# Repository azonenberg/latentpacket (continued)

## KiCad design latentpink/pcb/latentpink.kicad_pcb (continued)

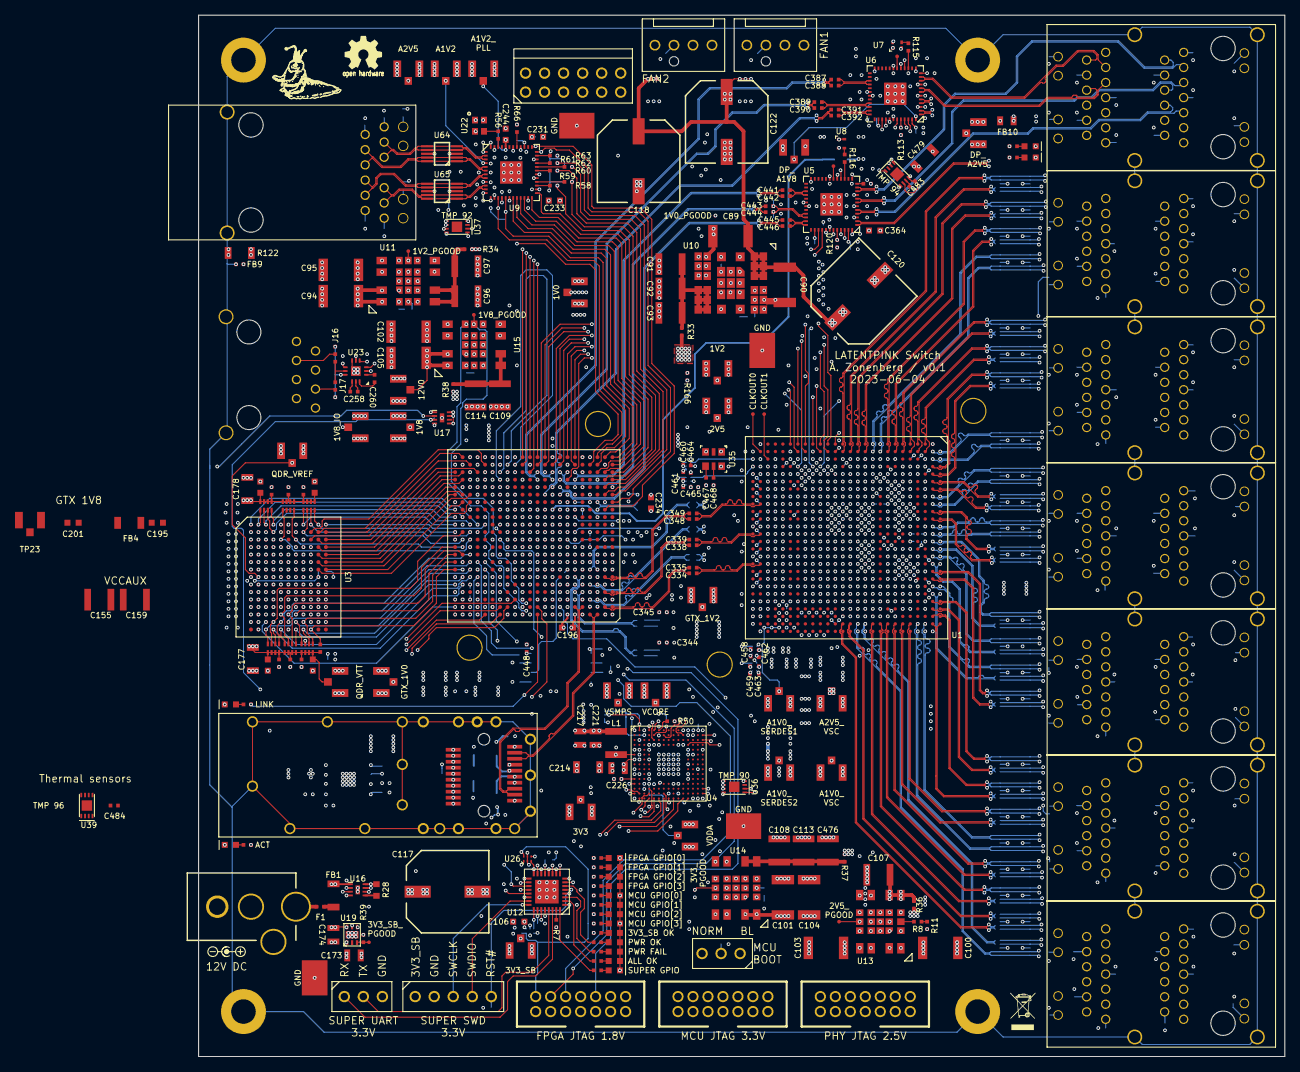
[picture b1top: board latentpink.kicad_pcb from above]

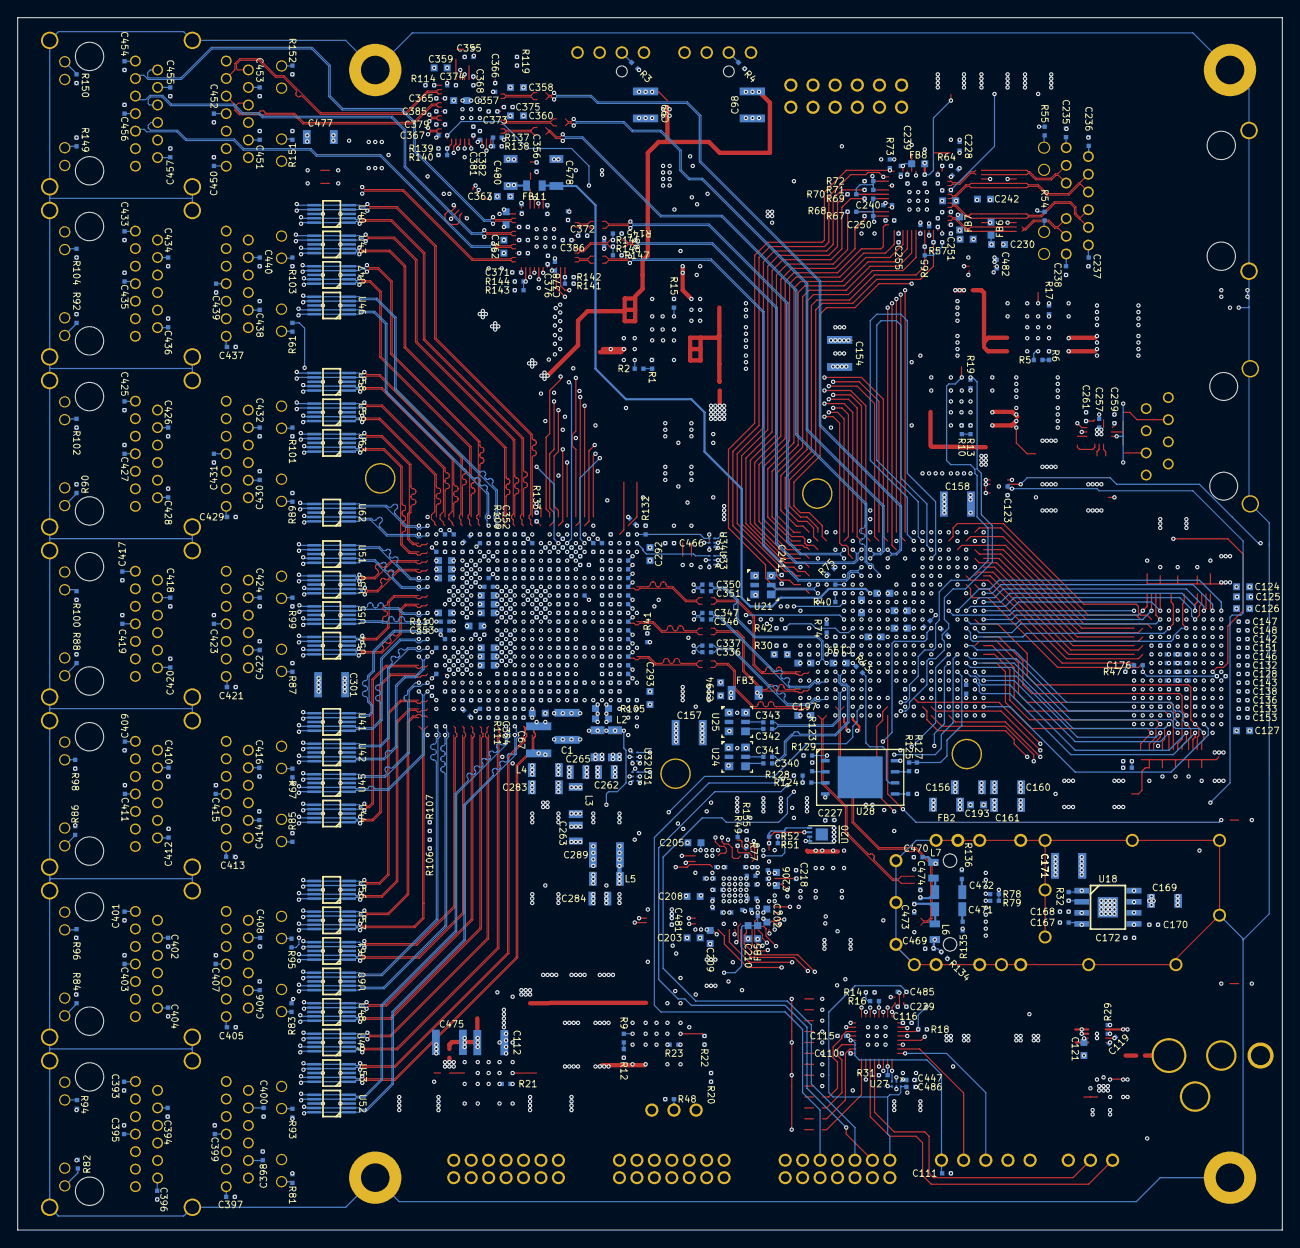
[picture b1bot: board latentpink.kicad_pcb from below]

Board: 8 copper layers, 145.0 x 139.0 mm, 827 parts (563 on the bottom side), 686 nets.

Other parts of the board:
C171#2: 220 uF; EIA_1210_CAP_NOSILK

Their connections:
/GND: C171#2.2; also elsewhere on the board
/QDR_VTT: C171#2.1; also elsewhere on the board

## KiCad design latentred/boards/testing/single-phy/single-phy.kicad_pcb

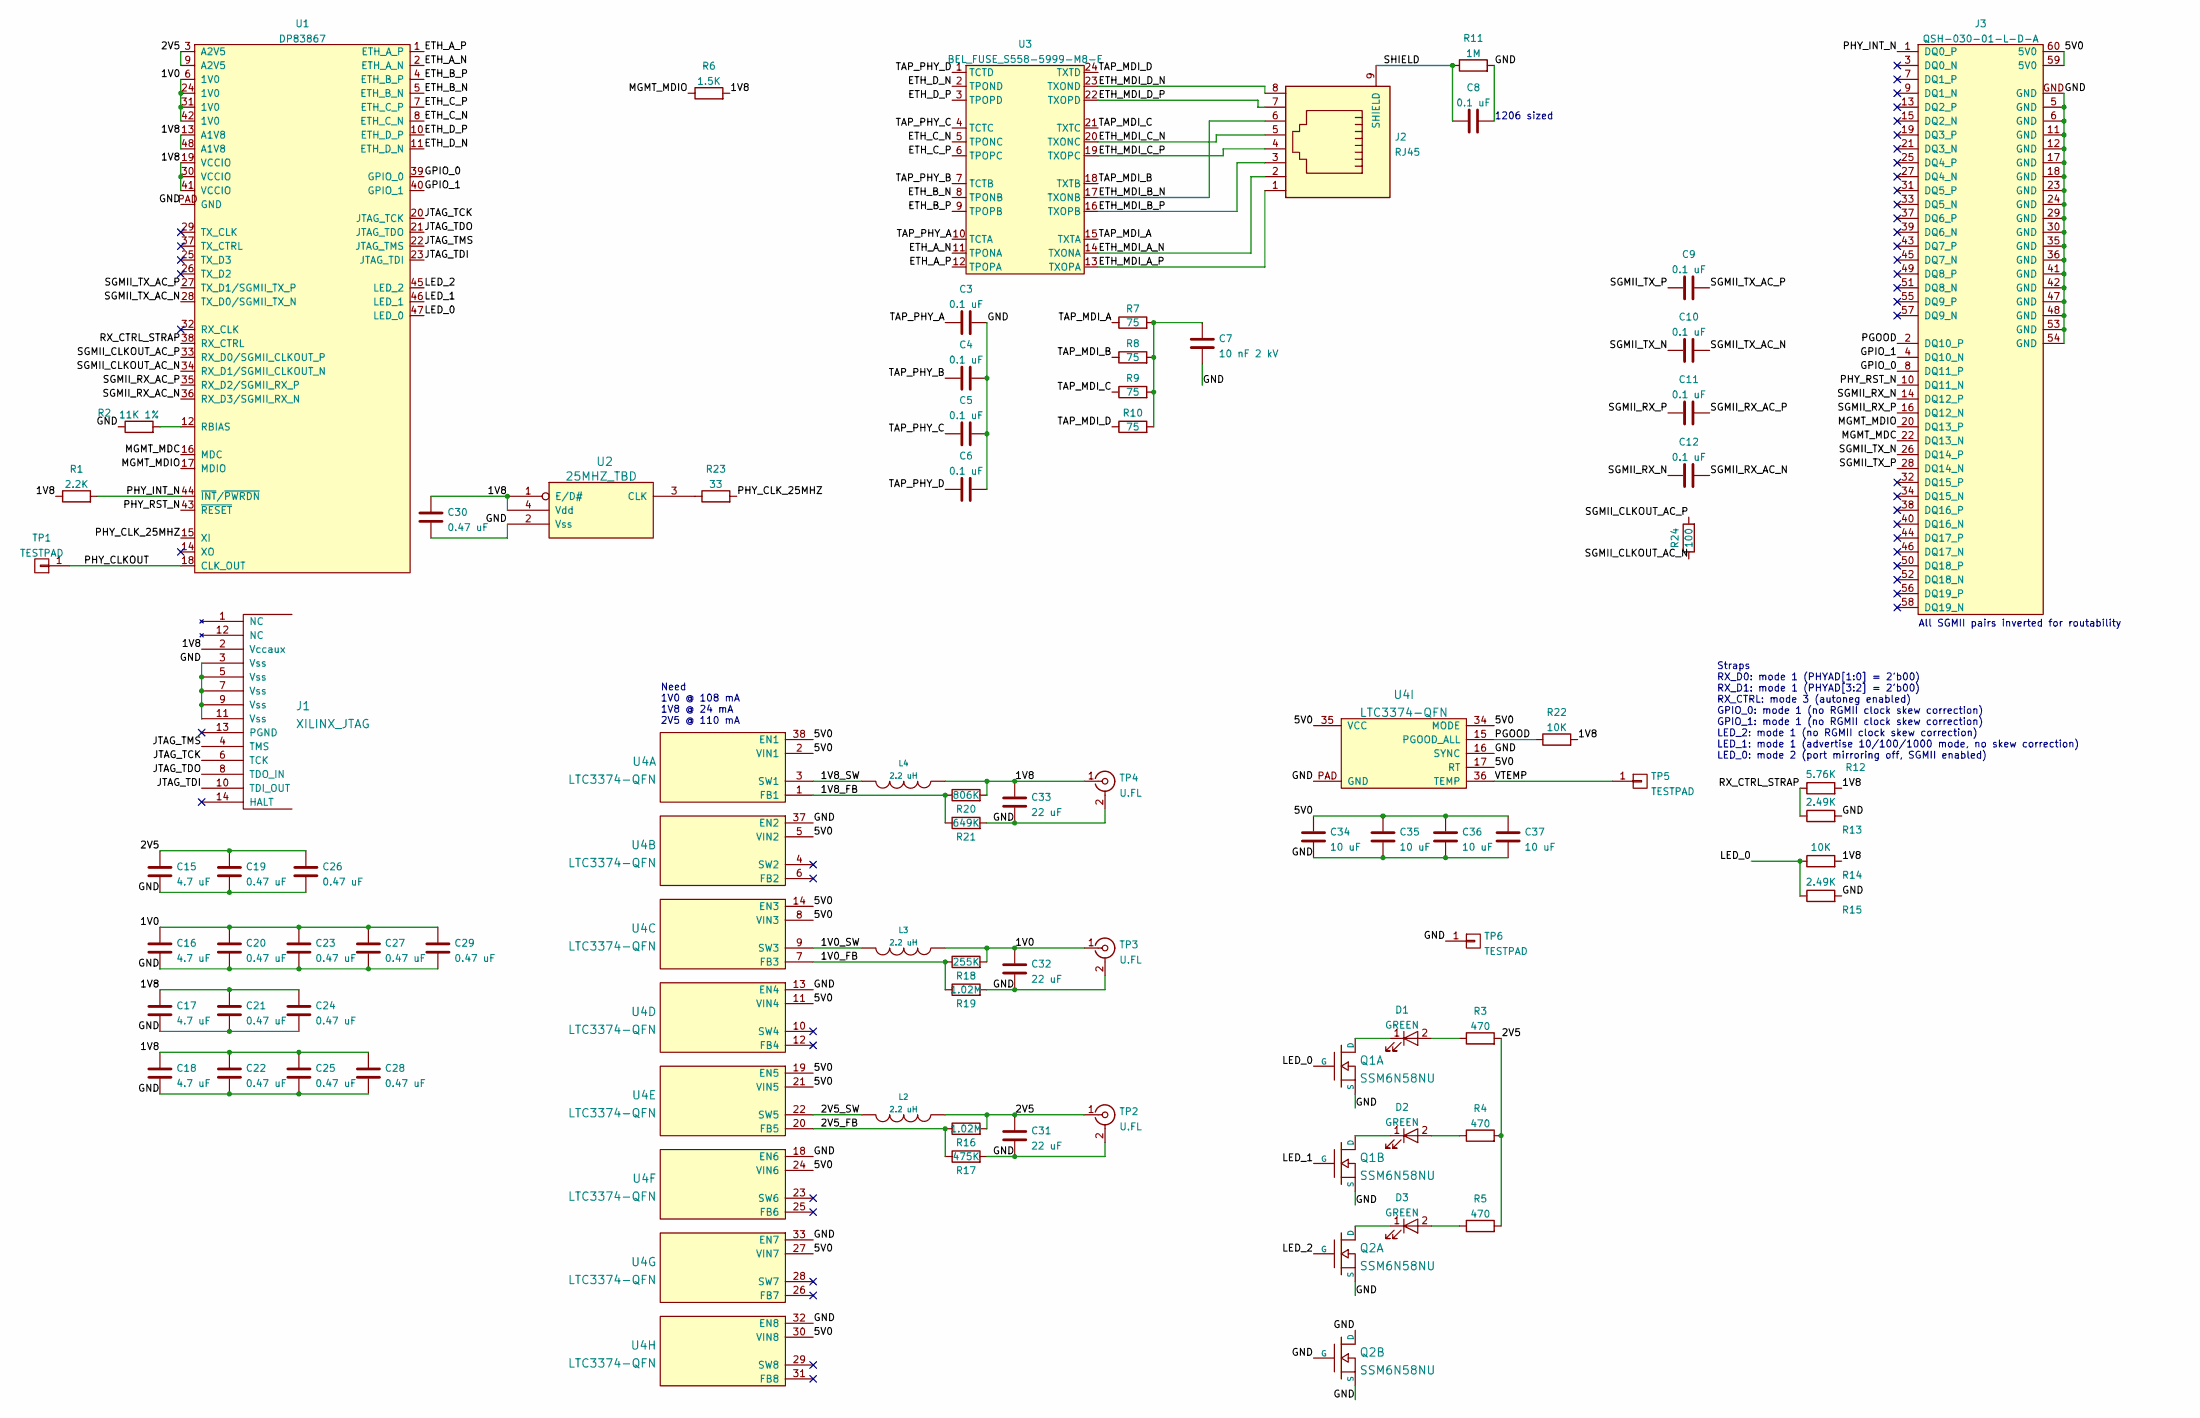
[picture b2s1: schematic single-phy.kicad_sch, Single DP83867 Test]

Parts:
C3, C4, C5, C6, C9, C10, C11, C12: 0.1 uF; EIA_0402_CAP_NOSILK
C7: 10 nF 2 kV; EIA_1812_CAP_NOSILK
C8: 0.1 uF; EIA_1206_CAP_NOSILK
C15, C16, C17, C18: 4.7 uF; EIA_0603_CAP_NOSILK
C19, C20, C21, C22, C23, C24, C25, C26, C27, C28, C29, C30: 0.47 uF; EIA_0402_CAP_NOSILK
C31, C32, C33: 22 uF; EIA_1206_CAP_NOSILK
C34, C35, C36, C37: 10 uF; EIA_0805_CAP_NOSILK
D1, D2, D3: GREEN; EIA_0603_LED
J1: XILINX_JTAG; XILINX_JTAG_PTH_MOLEX_0878311420
J2: RJ45; CONN_RJ45_BELSTEWART_SS-7188S-A-PG4-1-BA-xx
J3: QSH-030-01-L-D-A; CONN_SAMTEC_QSH-030-01-L-D-A
L2, L3, L4: 2.2 uH; EIA_1210_CAP_NOSILK
Q1, Q2: SSM6N58NU; DFN_6_0.65MM_2x2MM_GDS
R1: 2.2K; EIA_0402_RES_NOSILK
R2: 11K 1%; EIA_0402_RES_NOSILK
R3, R4, R5: 470; EIA_0402_RES_NOSILK
R6: 1.5K; EIA_0402_RES_NOSILK
R7, R8, R9, R10: 75; EIA_0402_RES_NOSILK
R11: 1M; EIA_1206_CAP_NOSILK
R12: 5.76K; EIA_0402_RES_NOSILK
R13, R15: 2.49K; EIA_0402_RES_NOSILK
R14, R22: 10K; EIA_0402_RES_NOSILK
R16, R19: 1.02M; EIA_0402_RES_NOSILK
R17: 475K; EIA_0402_RES_NOSILK
R18: 255K; EIA_0402_RES_NOSILK
R20: 806K; EIA_0402_RES_NOSILK
R21: 649K; EIA_0402_RES_NOSILK
R23: 33; EIA_0402_RES_NOSILK
R24: 100; EIA_0402_RES_NOSILK
TP1, TP5: TESTPAD; TESTPOINT_SMT_0.5MM
TP2, TP3, TP4: U.FL; CONN_U.FL_TE_1909763-1
TP6: TESTPAD; TESTPOINT_SMT_KEYSTONE_5016
U1: DP83867; QFN_48_0.5MM_7x7MM
U2: 25MHZ_TBD; OSCILLATOR_2.0x1.6
U3: BEL_FUSE_S558-5999-M8-F; BELFUSE_S558-5999-M8-F
U4: LTC3374-QFN; QFN_38_0.5MM_5x7MM

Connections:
/1V0: C16.1, C20.1, C23.1, C27.1, C29.1, C32.1, L3.1, R18.2, TP3.1 (In), U1.6 (1V0), U1.24 (1V0), U1.31 (1V0), U1.42 (1V0)
/1V0_FB: R18.1, R19.1, U4.7 (FB3)
/1V0_SW: L3.2, U4.9 (SW3)
/1V8: C17.1, C18.1, C21.1, C22.1, C24.1, C25.1, C28.1, C30.1, C33.1, J1.2 (Vccaux), L4.1, R1.1, R6.2, R12.2, R14.2, R20.2, R22.2, TP4.1 (In), U1.13 (A1V8), U1.19 (VCCIO), U1.30 (VCCIO), U1.41 (VCCIO), U1.48 (A1V8), U2.1 (E/D#), U2.4 (Vdd)
/1V8_FB: R20.1, R21.1, U4.1 (FB1)
/1V8_SW: L4.2, U4.3 (SW1)
/2V5: C15.1, C19.1, C26.1, C31.1, L2.1, R3.2, R4.2, R5.2, R16.2, TP2.1 (In), U1.3 (A2V5), U1.9 (A2V5)
/2V5_FB: R16.1, R17.1, U4.20 (FB5)
/2V5_SW: L2.2, U4.22 (SW5)
/5V0: C34.1, C35.1, C36.1, C37.1, J3.59 (5V0), J3.60 (5V0), U4.2 (VIN1), U4.5 (VIN2), U4.8 (VIN3), U4.11 (VIN4), U4.14 (EN3), U4.17 (RT), U4.19 (EN5), U4.21 (VIN5), U4.24 (VIN6), U4.27 (VIN7), U4.30 (VIN8), U4.34 (MODE), U4.35 (VCC), U4.38 (EN1)
/ETH_A_N: U1.2 (ETH_A_N), U3.11 (TPONA)
/ETH_A_P: U1.1 (ETH_A_P), U3.12 (TPOPA)
/ETH_B_N: U1.5 (ETH_B_N), U3.8 (TPONB)
/ETH_B_P: U1.4 (ETH_B_P), U3.9 (TPOPB)
/ETH_C_N: U1.8 (ETH_C_N), U3.5 (TPONC)
/ETH_C_P: U1.7 (ETH_C_P), U3.6 (TPOPC)
/ETH_D_N: U1.11 (ETH_D_N), U3.2 (TPOND)
/ETH_D_P: U1.10 (ETH_D_P), U3.3 (TPOPD)
/ETH_MDI_A_N: J2.2, U3.14 (TXONA)
/ETH_MDI_A_P: J2.1, U3.13 (TXOPA)
/ETH_MDI_B_N: J2.6, U3.17 (TXONB)
/ETH_MDI_B_P: J2.3, U3.16 (TXOPB)
/ETH_MDI_C_N: J2.5, U3.20 (TXONC)
/ETH_MDI_C_P: J2.4, U3.19 (TXOPC)
/ETH_MDI_D_N: J2.8, U3.23 (TXOND)
/ETH_MDI_D_P: J2.7, U3.22 (TXOPD)
/GND: C3.2, C4.2, C5.2, C6.2, C7.2, C8.2, C15.2, C16.2, C17.2, C18.2, C19.2, C20.2, C21.2, C22.2, C23.2, C24.2, C25.2, C26.2, C27.2, C28.2, C29.2, C30.2, C31.2, C32.2, C33.2, C34.2, C35.2, C36.2, C37.2, J1.3 (Vss), J1.5 (Vss), J1.7 (Vss), J1.9 (Vss), J1.11 (Vss), J3.5 (GND), J3.6 (GND), J3.11 (GND), J3.12 (GND), J3.17 (GND), J3.18 (GND), J3.23 (GND), J3.24 (GND), J3.29 (GND), J3.30 (GND), J3.35 (GND), J3.36 (GND), J3.41 (GND), J3.42 (GND), J3.47 (GND), J3.48 (GND), J3.53 (GND), J3.54 (GND), J3.GND, Q1.S1 (S), Q1.S2 (S), Q2.D2 (D), Q2.G2 (G), Q2.S1 (S), Q2.S2 (S), R2.1, R11.2, R13.2, R15.2, R17.2, R19.2, R21.2, TP2.2 (Ext), TP3.2 (Ext), TP4.2 (Ext), TP6.1, U1.PAD (GND), U2.2 (Vss), U4.13 (EN4), U4.16 (SYNC), U4.18 (EN6), U4.32 (EN8), U4.33 (EN7), U4.37 (EN2), U4.PAD (GND)
/GPIO_0: J3.8 (DQ11_P), U1.39 (GPIO_0)
/GPIO_1: J3.4 (DQ10_N), U1.40 (GPIO_1)
/JTAG_TCK: J1.6 (TCK), U1.20 (JTAG_TCK)
/JTAG_TDI: J1.10 (TDI_OUT), U1.23 (JTAG_TDI)
/JTAG_TDO: J1.8 (TDO_IN), U1.21 (JTAG_TDO)
/JTAG_TMS: J1.4 (TMS), U1.22 (JTAG_TMS)
/LED_0: Q1.G1 (G), R14.1, R15.1, U1.47 (LED_0)
/LED_1: Q1.G2 (G), U1.46 (LED_1)
/LED_2: Q2.G1 (G), U1.45 (LED_2)
/MGMT_MDC: J3.22 (DQ13_N), U1.16 (MDC)
/MGMT_MDIO: J3.20 (DQ13_P), R6.1, U1.17 (MDIO)
/PGOOD: J3.2 (DQ10_P), R22.1, U4.15 (PGOOD_ALL)
/PHY_CLKOUT: TP1.1, U1.18 (CLK_OUT)
/PHY_CLK_25MHZ: R23.2, U1.15 (XI)
/PHY_INT_N: J3.1 (DQ0_P), R1.2, U1.44 (~INT/~PWRDN)
/PHY_RST_N: J3.10 (DQ11_N), U1.43 (~RESET)
/RX_CTRL_STRAP: R12.1, R13.1, U1.38 (RX_CTRL)
/SGMII_CLKOUT_AC_N: R24.1, U1.34 (RX_D1/SGMII_CLKOUT_N)
/SGMII_CLKOUT_AC_P: R24.2, U1.33 (RX_D0/SGMII_CLKOUT_P)
/SGMII_RX_AC_N: C12.2, U1.36 (RX_D3/SGMII_RX_N)
/SGMII_RX_AC_P: C11.2, U1.35 (RX_D2/SGMII_RX_P)
/SGMII_RX_N: C12.1, J3.14 (DQ12_P)
/SGMII_RX_P: C11.1, J3.16 (DQ12_N)
/SGMII_TX_AC_N: C10.2, U1.28 (TX_D0/SGMII_TX_N)
/SGMII_TX_AC_P: C9.2, U1.27 (TX_D1/SGMII_TX_P)
/SGMII_TX_N: C10.1, J3.26 (DQ14_P)
/SGMII_TX_P: C9.1, J3.28 (DQ14_N)
/SHIELD: C8.1, J2.9 (SHIELD), R11.1
/TAP_MDI_A: R7.1, U3.15 (TXTA)
/TAP_MDI_B: R8.1, U3.18 (TXTB)
/TAP_MDI_C: R9.1, U3.21 (TXTC)
/TAP_MDI_D: R10.1, U3.24 (TXTD)
/TAP_PHY_A: C3.1, U3.10 (TCTA)
/TAP_PHY_B: C4.1, U3.7 (TCTB)
/TAP_PHY_C: C5.1, U3.4 (TCTC)
/TAP_PHY_D: C6.1, U3.1 (TCTD)
/VTEMP: TP5.1, U4.36 (TEMP)
unnamed: C7.1, R7.2, R8.2, R9.2, R10.2
unnamed: D1.2 (A), R3.1
unnamed: D3.2 (A), R5.1
unnamed: D1.1 (K), Q1.D1 (D)
unnamed: D2.1 (K), Q1.D2 (D)
unnamed: D3.1 (K), Q2.D1 (D)
unnamed: R2.2, U1.12 (RBIAS)
unnamed: D2.2 (A), R4.1
unnamed: R23.1, U2.3 (CLK)

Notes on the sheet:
All SGMII pairs inverted for routability
Straps RX_D0: mode 1 (PHYAD[1:0] = 2'b00) RX_D1: mode 1 (PHYAD[3:2] = 2'b00) RX_CTRL: mode 3 (autoneg enabled) GPIO_0: mode 1 (no RGMII clock skew correction) GPIO_1: mode 1 (no RGMII clock skew correction) LED_2: mode 1 (no RGMII clock skew correction) LED_1: mode 1 (advertise 10/100/1000 mode, no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
1206 sized
Need 1V0 @ 108 mA 1V8 @ 24 mA 2V5 @ 110 mA

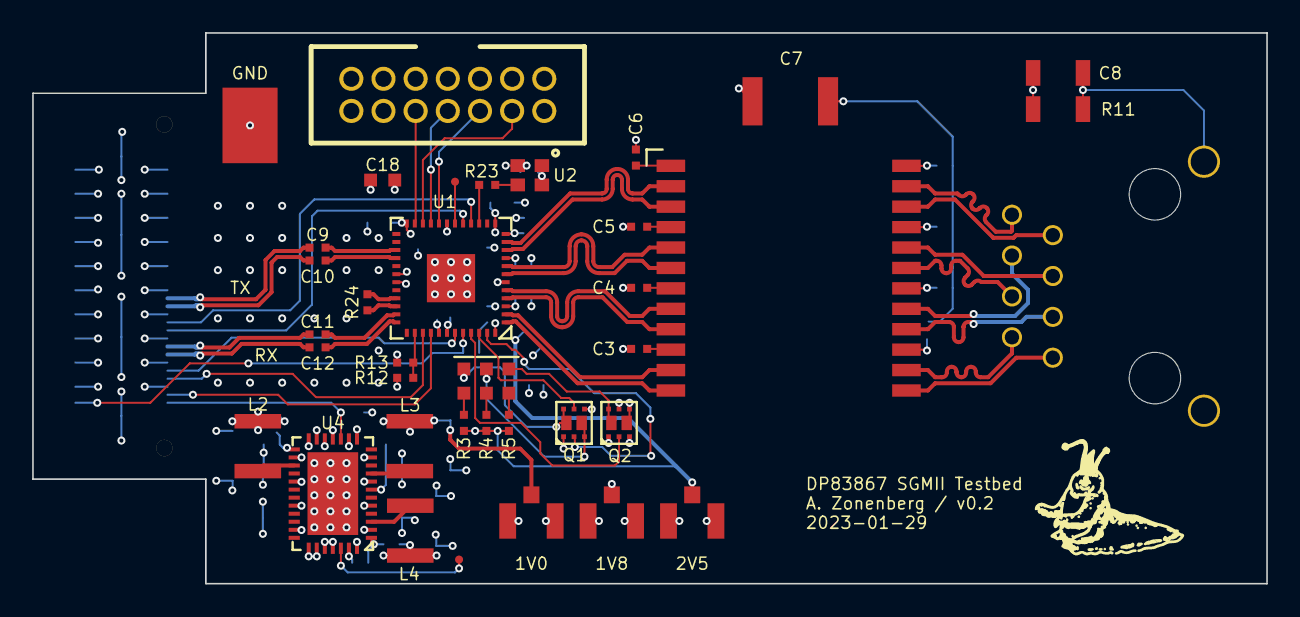
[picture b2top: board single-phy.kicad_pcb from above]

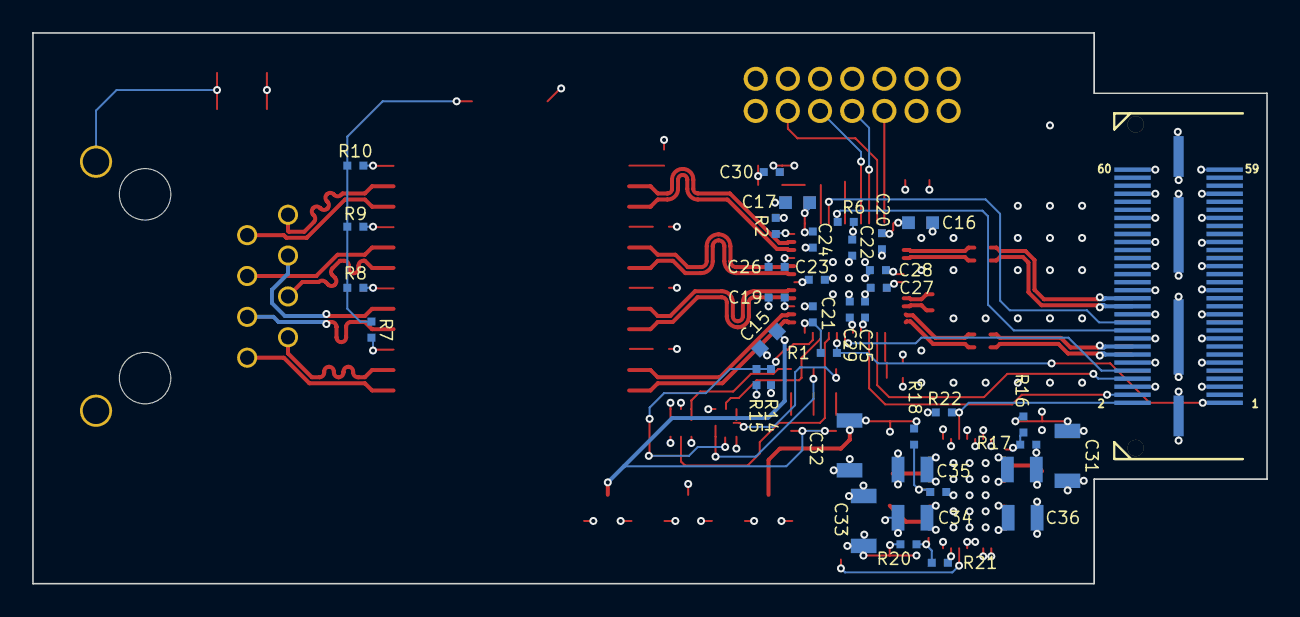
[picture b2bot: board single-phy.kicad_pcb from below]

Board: 4 copper layers, 76.8 x 34.2 mm, 78 parts (39 on the bottom side), 73 nets.

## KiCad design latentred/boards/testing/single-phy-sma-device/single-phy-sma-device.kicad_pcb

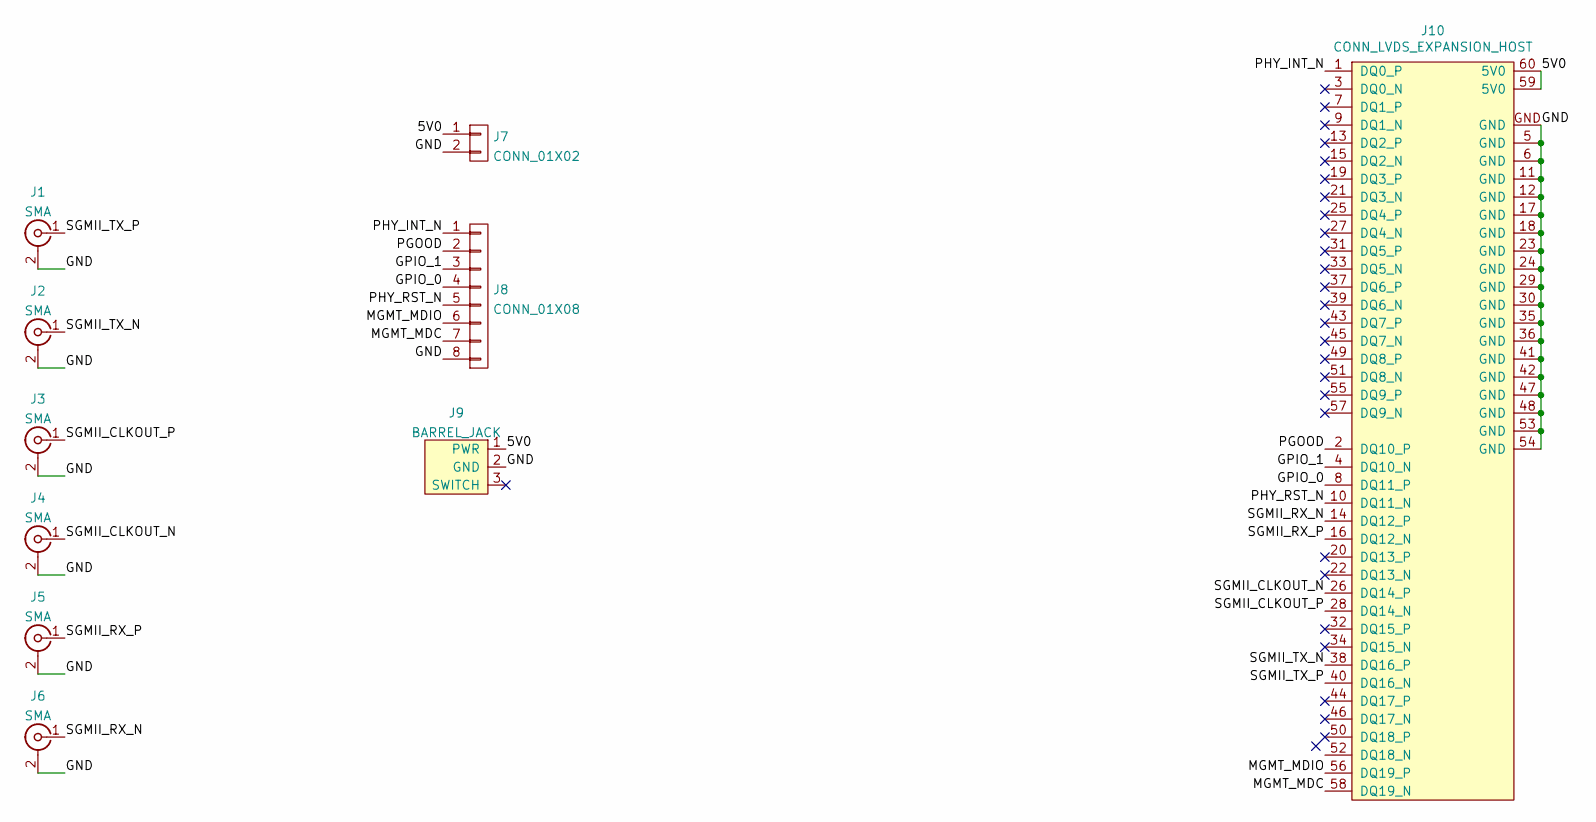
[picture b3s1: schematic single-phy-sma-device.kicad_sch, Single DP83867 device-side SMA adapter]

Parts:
J1, J2, J3, J4, J5, J6: SMA; CONN_SMA_EDGE_SAMTEC_SMA_J_P_H_ST_EM1
J7: CONN_01X02; CONN_HEADER_2.54MM_1x2
J8: CONN_01X08; CONN_HEADER_2.54MM_1x8
J9: BARREL_JACK; CONN_CUI_PJ-058BH_HIPWR_BARREL_NOSLOT
J10: CONN_LVDS_EXPANSION_HOST; CONN_SAMTEC_QTH-030-01-L-D-A

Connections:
/5V0: J7.1, J9.1 (PWR), J10.59 (5V0), J10.60 (5V0)
/GND: J1.2 (Ext), J2.2 (Ext), J3.2 (Ext), J4.2 (Ext), J5.2 (Ext), J6.2 (Ext), J7.2, J8.8, J9.2 (GND), J10.5 (GND), J10.6 (GND), J10.11 (GND), J10.12 (GND), J10.17 (GND), J10.18 (GND), J10.23 (GND), J10.24 (GND), J10.29 (GND), J10.30 (GND), J10.35 (GND), J10.36 (GND), J10.41 (GND), J10.42 (GND), J10.47 (GND), J10.48 (GND), J10.53 (GND), J10.54 (GND), J10.GND
/GPIO_0: J8.4, J10.8 (DQ11_P)
/GPIO_1: J8.3, J10.4 (DQ10_N)
/MGMT_MDC: J8.7, J10.58 (DQ19_N)
/MGMT_MDIO: J8.6, J10.56 (DQ19_P)
/PGOOD: J8.2, J10.2 (DQ10_P)
/PHY_INT_N: J8.1, J10.1 (DQ0_P)
/PHY_RST_N: J8.5, J10.10 (DQ11_N)
/SGMII_CLKOUT_N: J4.1 (In), J10.26 (DQ14_P)
/SGMII_CLKOUT_P: J3.1 (In), J10.28 (DQ14_N)
/SGMII_RX_N: J6.1 (In), J10.14 (DQ12_P)
/SGMII_RX_P: J5.1 (In), J10.16 (DQ12_N)
/SGMII_TX_N: J2.1 (In), J10.38 (DQ16_P)
/SGMII_TX_P: J1.1 (In), J10.40 (DQ16_N)

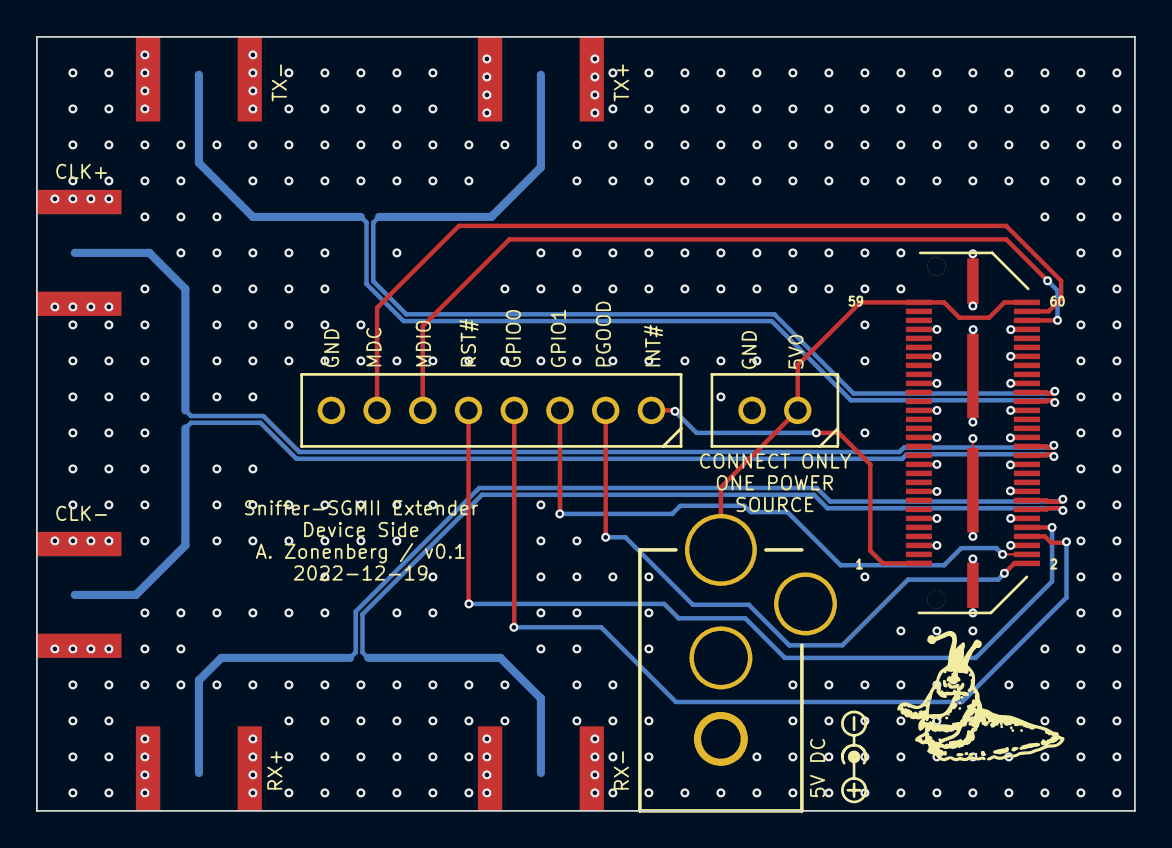
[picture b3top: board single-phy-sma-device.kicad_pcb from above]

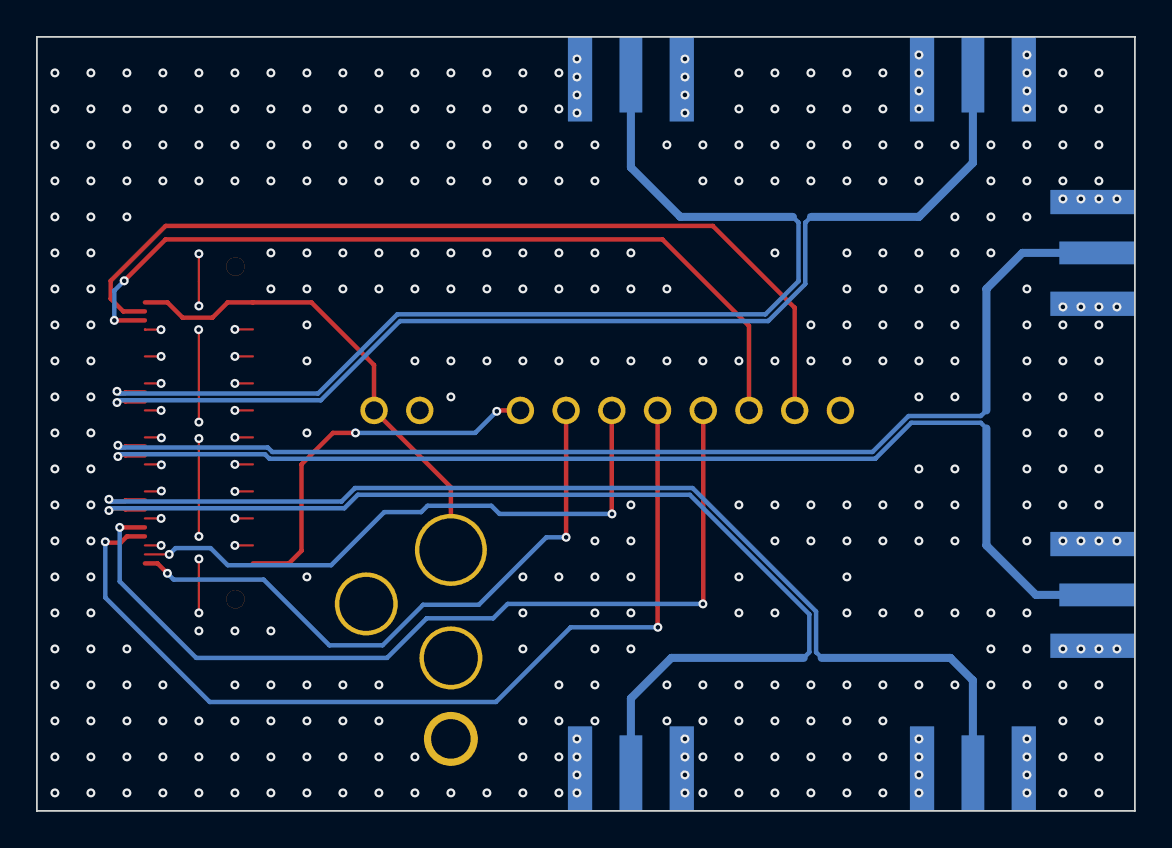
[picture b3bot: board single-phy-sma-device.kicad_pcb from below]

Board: 4 copper layers, 61.0 x 43.0 mm, 10 parts (6 on the bottom side), 15 nets.

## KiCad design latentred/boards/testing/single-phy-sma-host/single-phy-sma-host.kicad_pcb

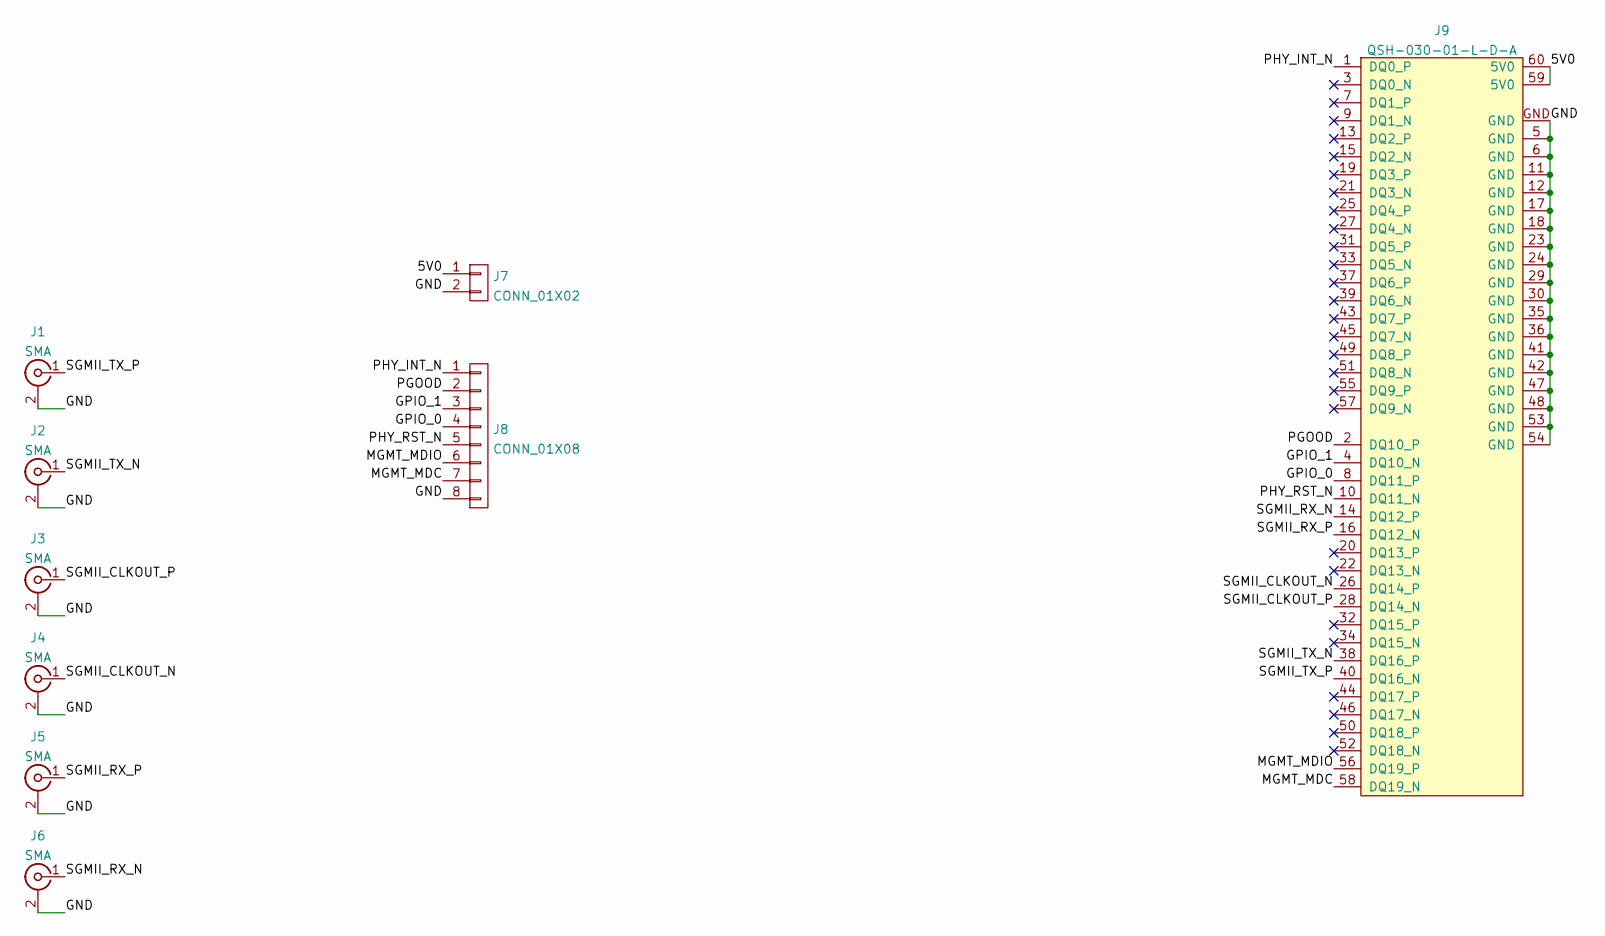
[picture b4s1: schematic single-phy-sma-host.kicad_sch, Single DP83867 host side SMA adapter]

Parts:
J1, J2, J3, J4, J5, J6: SMA; CONN_SMA_EDGE_SAMTEC_SMA_J_P_H_ST_EM1
J7: CONN_01X02; CONN_HEADER_2.54MM_1x2
J8: CONN_01X08; CONN_HEADER_2.54MM_1x8
J9: QSH-030-01-L-D-A; CONN_SAMTEC_QSH-030-01-L-D-A

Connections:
/5V0: J7.1, J9.59 (5V0), J9.60 (5V0)
/GND: J1.2 (Ext), J2.2 (Ext), J3.2 (Ext), J4.2 (Ext), J5.2 (Ext), J6.2 (Ext), J7.2, J8.8, J9.5 (GND), J9.6 (GND), J9.11 (GND), J9.12 (GND), J9.17 (GND), J9.18 (GND), J9.23 (GND), J9.24 (GND), J9.29 (GND), J9.30 (GND), J9.35 (GND), J9.36 (GND), J9.41 (GND), J9.42 (GND), J9.47 (GND), J9.48 (GND), J9.53 (GND), J9.54 (GND), J9.GND
/GPIO_0: J8.4, J9.8 (DQ11_P)
/GPIO_1: J8.3, J9.4 (DQ10_N)
/MGMT_MDC: J8.7, J9.58 (DQ19_N)
/MGMT_MDIO: J8.6, J9.56 (DQ19_P)
/PGOOD: J8.2, J9.2 (DQ10_P)
/PHY_INT_N: J8.1, J9.1 (DQ0_P)
/PHY_RST_N: J8.5, J9.10 (DQ11_N)
/SGMII_CLKOUT_N: J4.1 (In), J9.26 (DQ14_P)
/SGMII_CLKOUT_P: J3.1 (In), J9.28 (DQ14_N)
/SGMII_RX_N: J6.1 (In), J9.14 (DQ12_P)
/SGMII_RX_P: J5.1 (In), J9.16 (DQ12_N)
/SGMII_TX_N: J2.1 (In), J9.38 (DQ16_P)
/SGMII_TX_P: J1.1 (In), J9.40 (DQ16_N)

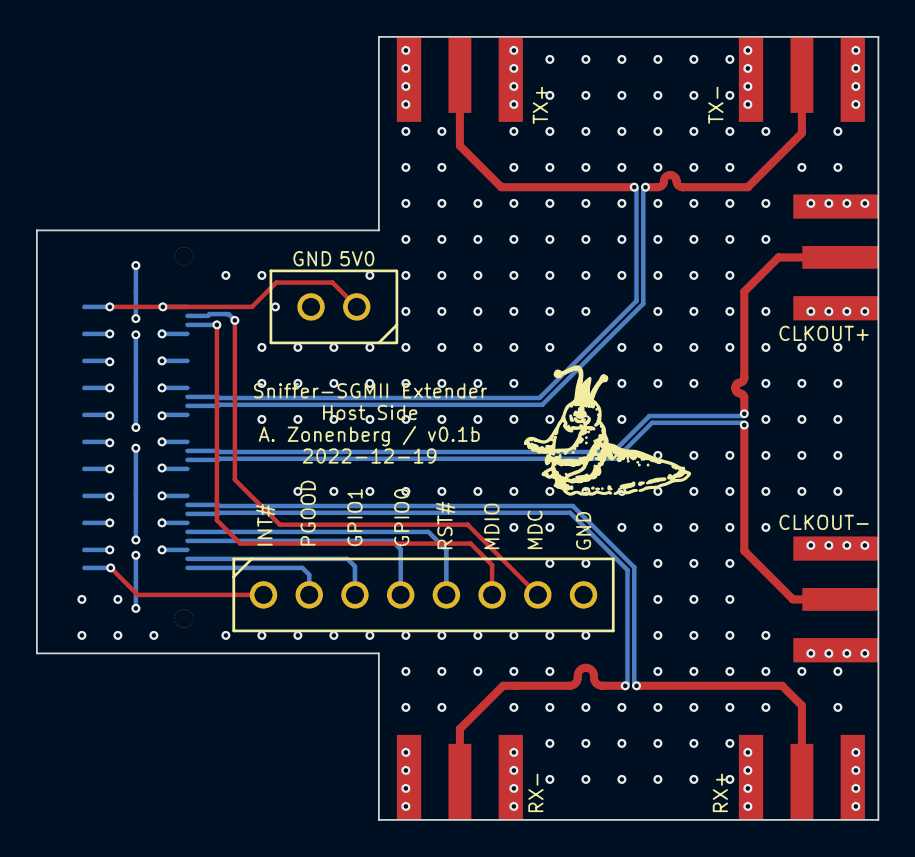
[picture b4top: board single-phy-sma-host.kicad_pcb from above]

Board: 4 copper layers, 46.8 x 43.5 mm, 9 parts (1 on the bottom side), 15 nets.

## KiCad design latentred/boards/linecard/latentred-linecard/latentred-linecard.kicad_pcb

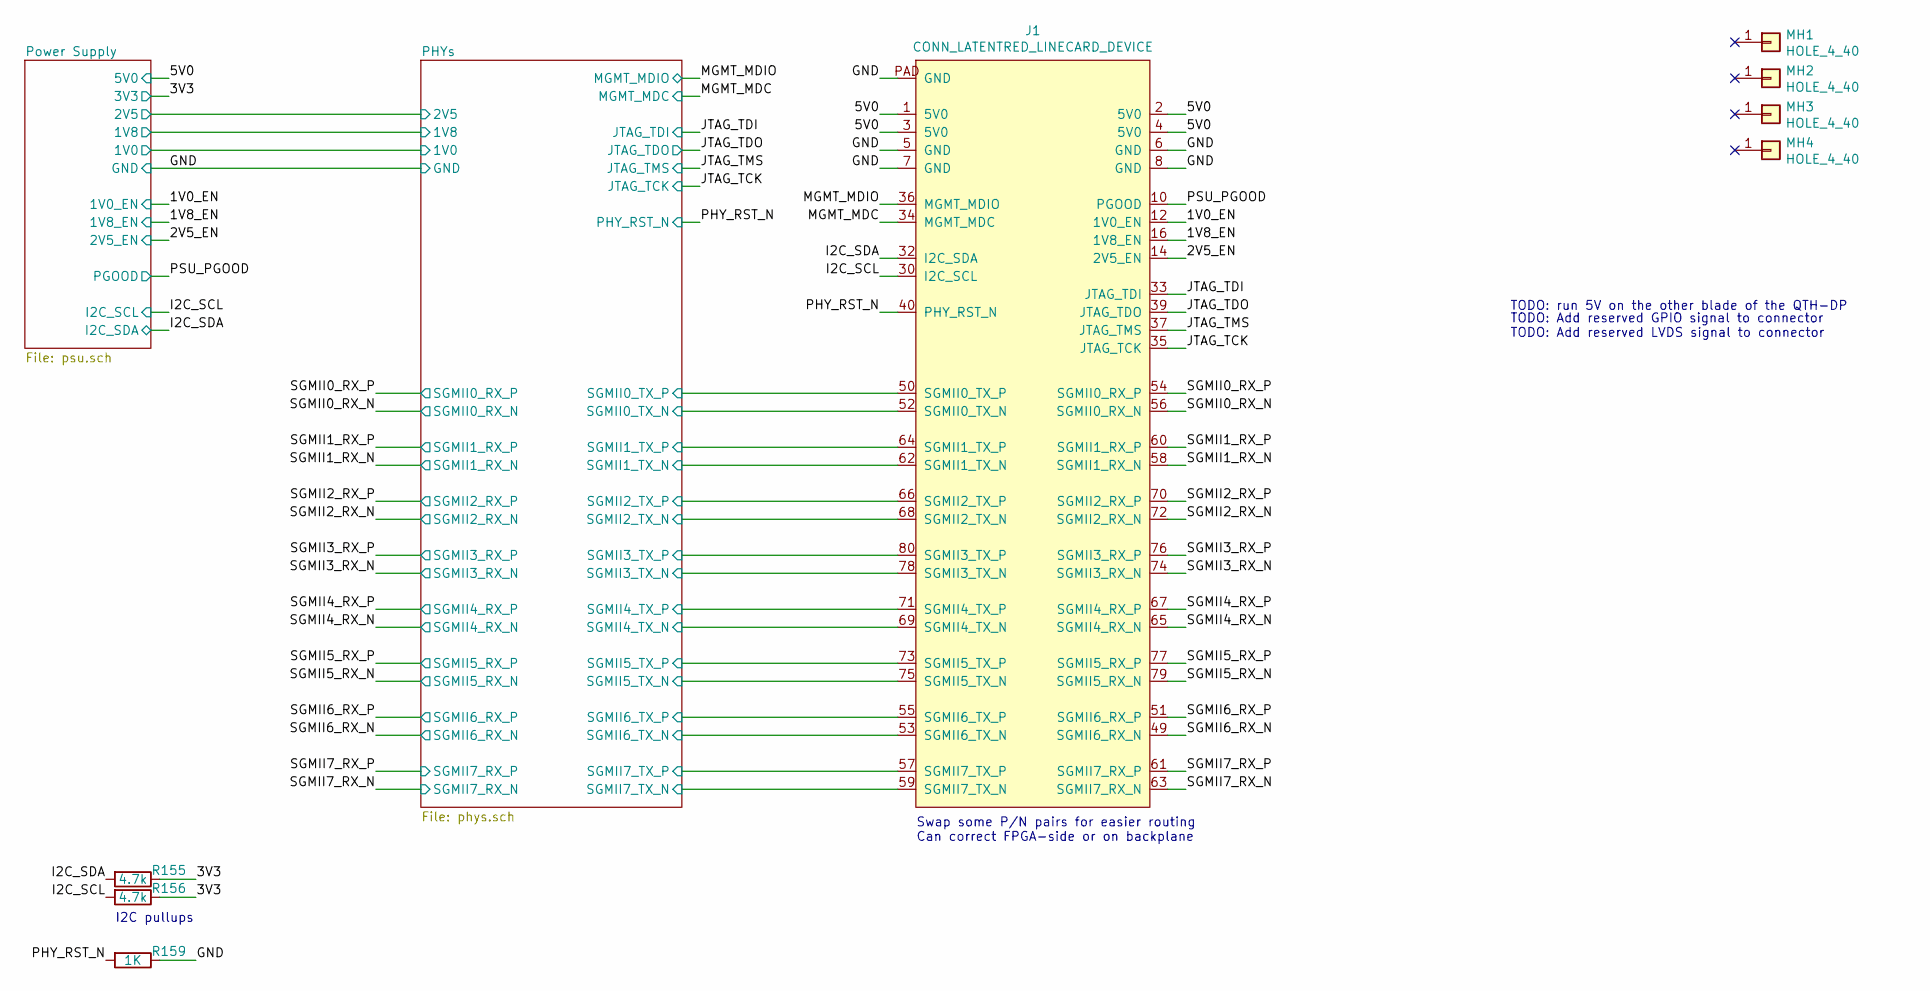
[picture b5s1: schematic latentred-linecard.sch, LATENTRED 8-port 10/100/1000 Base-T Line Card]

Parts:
J1: CONN_LATENTRED_LINECARD_DEVICE; CONN_SAMTEC_QTH-040-01-L-D-DP-A
MH1, MH2, MH3, MH4: HOLE_4_40; MECHANICAL_CLEARANCEHOLE_4_40
R155, R156: 4.7k; EIA_0402_RES_NOSILK
R159: 1K; EIA_0402_RES_NOSILK

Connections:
/1V0_EN: J1.12 (1V0_EN); also elsewhere on the board
/1V8_EN: J1.16 (1V8_EN); also elsewhere on the board
/2V5_EN: J1.14 (2V5_EN); also elsewhere on the board
/3V3: R155.1, R156.1; also elsewhere on the board
/5V0: J1.1 (5V0), J1.2 (5V0), J1.3 (5V0), J1.4 (5V0); also elsewhere on the board
/GND: J1.5 (GND), J1.6 (GND), J1.7 (GND), J1.8 (GND), J1.PAD (GND), R159.1; also elsewhere on the board
/I2C_SCL: J1.30 (I2C_SCL), R156.2; also elsewhere on the board
/I2C_SDA: J1.32 (I2C_SDA), R155.2; also elsewhere on the board
/JTAG_TCK: J1.35 (JTAG_TCK); also elsewhere on the board
/JTAG_TDI: J1.33 (JTAG_TDI); also elsewhere on the board
/JTAG_TDO: J1.39 (JTAG_TDO); also elsewhere on the board
/JTAG_TMS: J1.37 (JTAG_TMS); also elsewhere on the board
/MGMT_MDC: J1.34 (MGMT_MDC); also elsewhere on the board
/MGMT_MDIO: J1.36 (MGMT_MDIO); also elsewhere on the board
/PHY_RST_N: J1.40 (PHY_RST_N), R159.2; also elsewhere on the board
/PHYs/SGMII0_TX_N: J1.52 (SGMII0_TX_N); also elsewhere on the board
/PHYs/SGMII0_TX_P: J1.50 (SGMII0_TX_P); also elsewhere on the board
/PHYs/SGMII1_TX_N: J1.62 (SGMII1_TX_N); also elsewhere on the board
/PHYs/SGMII1_TX_P: J1.64 (SGMII1_TX_P); also elsewhere on the board
/PHYs/SGMII2_TX_N: J1.68 (SGMII2_TX_N); also elsewhere on the board
/PHYs/SGMII2_TX_P: J1.66 (SGMII2_TX_P); also elsewhere on the board
/PHYs/SGMII3_TX_N: J1.78 (SGMII3_TX_N); also elsewhere on the board
/PHYs/SGMII3_TX_P: J1.80 (SGMII3_TX_P); also elsewhere on the board
/PHYs/SGMII4_TX_N: J1.69 (SGMII4_TX_N); also elsewhere on the board
/PHYs/SGMII4_TX_P: J1.71 (SGMII4_TX_P); also elsewhere on the board
/PHYs/SGMII5_TX_N: J1.75 (SGMII5_TX_N); also elsewhere on the board
/PHYs/SGMII5_TX_P: J1.73 (SGMII5_TX_P); also elsewhere on the board
/PHYs/SGMII6_TX_N: J1.53 (SGMII6_TX_N); also elsewhere on the board
/PHYs/SGMII6_TX_P: J1.55 (SGMII6_TX_P); also elsewhere on the board
/PHYs/SGMII7_TX_N: J1.59 (SGMII7_TX_N); also elsewhere on the board
/PHYs/SGMII7_TX_P: J1.57 (SGMII7_TX_P); also elsewhere on the board
/PSU_PGOOD: J1.10 (PGOOD); also elsewhere on the board
/SGMII0_RX_N: J1.56 (SGMII0_RX_N); also elsewhere on the board
/SGMII0_RX_P: J1.54 (SGMII0_RX_P); also elsewhere on the board
/SGMII1_RX_N: J1.58 (SGMII1_RX_N); also elsewhere on the board
/SGMII1_RX_P: J1.60 (SGMII1_RX_P); also elsewhere on the board
/SGMII2_RX_N: J1.72 (SGMII2_RX_N); also elsewhere on the board
/SGMII2_RX_P: J1.70 (SGMII2_RX_P); also elsewhere on the board
/SGMII3_RX_N: J1.74 (SGMII3_RX_N); also elsewhere on the board
/SGMII3_RX_P: J1.76 (SGMII3_RX_P); also elsewhere on the board
/SGMII4_RX_N: J1.65 (SGMII4_RX_N); also elsewhere on the board
/SGMII4_RX_P: J1.67 (SGMII4_RX_P); also elsewhere on the board
/SGMII5_RX_N: J1.79 (SGMII5_RX_N); also elsewhere on the board
/SGMII5_RX_P: J1.77 (SGMII5_RX_P); also elsewhere on the board
/SGMII6_RX_N: J1.49 (SGMII6_RX_N); also elsewhere on the board
/SGMII6_RX_P: J1.51 (SGMII6_RX_P); also elsewhere on the board
/SGMII7_RX_N: J1.63 (SGMII7_RX_N); also elsewhere on the board
/SGMII7_RX_P: J1.61 (SGMII7_RX_P); also elsewhere on the board

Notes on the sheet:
I2C pullups
TODO: run 5V on the other blade of the QTH-DP
TODO: Add reserved GPIO signal to connector TODO: Add reserved LVDS signal to connector
Swap some P/N pairs for easier routing Can correct FPGA-side or on backplane
